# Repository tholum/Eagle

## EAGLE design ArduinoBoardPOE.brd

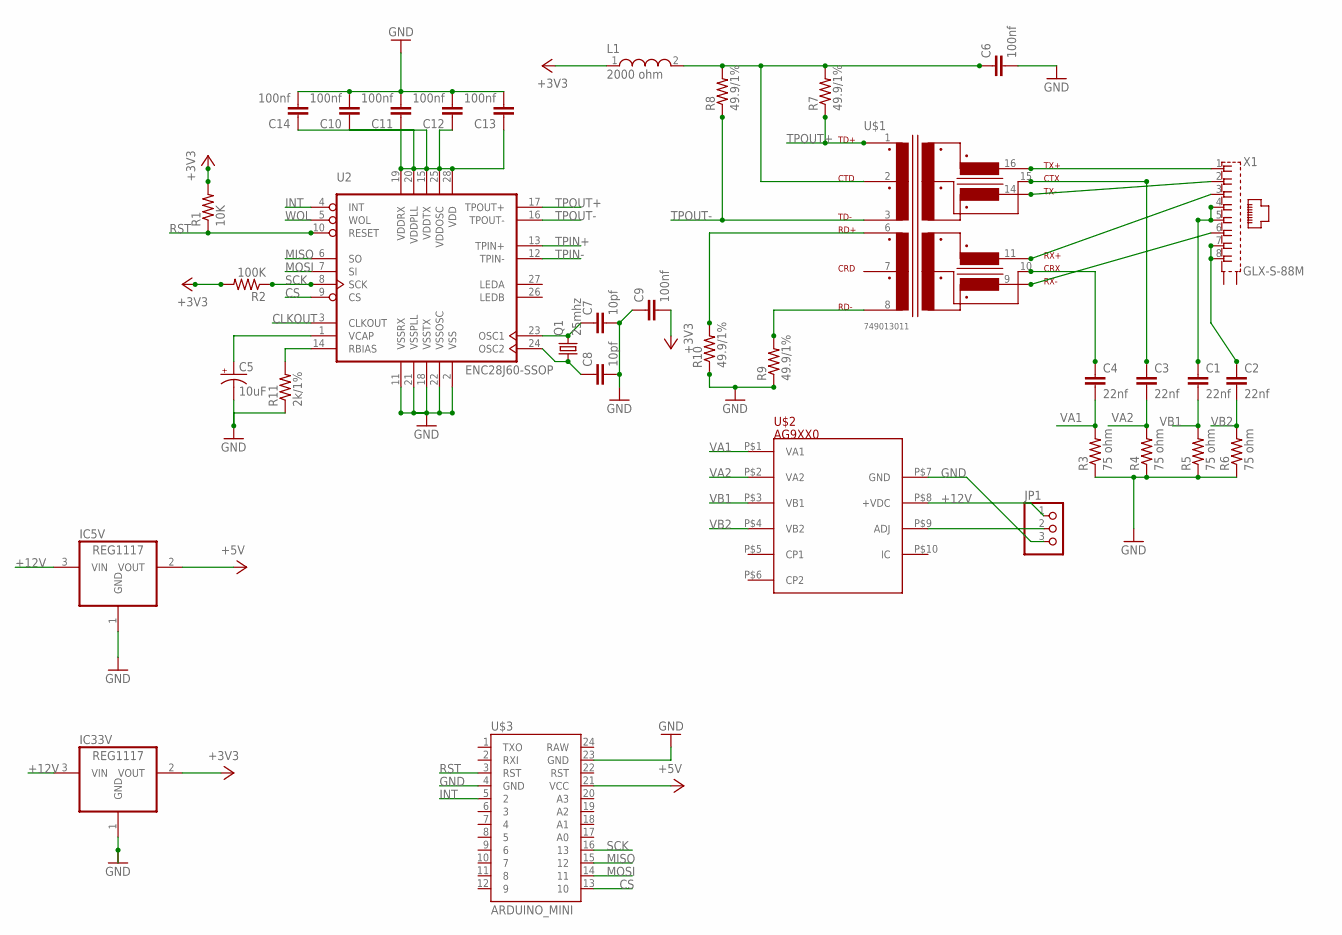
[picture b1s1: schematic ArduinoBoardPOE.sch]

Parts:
C1, C2, C3, C4: 22nf; 0805
C5: 10uF; EIA3216
C6, C9, C10, C11, C12, C13, C14: 100nf; 0805
C7, C8: 10pf; 0805
IC5V, IC33V: REG1117; SOT223
JP1: PINHD-1X3; 1X03
L1: 2000 ohm; WE-CBA_0805(W=3)
Q1: 25mhz; HC49UP
R1: 10K; 0805
R2: 100K; 0805
R3, R4, R5, R6: 75 ohm; 0805
R7, R8, R9, R10: 49.9/1%; 0805
R11: 2k/1%; R0805
U2: ENC28J60-SSOP; SSOP28
U$1: 749013011
U$2: AG9XX0; AG9000
U$3: ARDUINO_MINI
X1: GLX-S-88M

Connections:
+3V3: C9.2, IC33V.2 (VOUT), L1.1, R1.2, R2.2
+5V: IC5V.2 (VOUT), U$3.21 (VCC)
+12V: IC5V.3 (VIN), IC33V.3 (VIN), JP1.1, U$2.P$8 (+VDC)
CLKOUT: U2.3 (CLKOUT)
CS: U2.9 (CS), U$3.13 (10)
GND: C5.C (-), C6.2, C7.2, C8.2, C9.1, C10.2, C11.2, C12.2, C13.2, C14.2, IC5V.1 (GND), IC33V.1 (GND), JP1.3, R3.1, R4.1, R5.1, R6.1, R9.1, R10.1, R11.1, U2.2 (VSS), U2.11 (VSSRX), U2.18 (VSSTX), U2.21 (VSSPLL), U2.22 (VSSOSC), U$2.P$7 (GND), U$3.4 (GND), U$3.23 (GND)
INT: U2.4 (INT), U$3.5 (2)
MISO: U2.6 (SO), U$3.15 (12)
MOSI: U2.7 (SI), U$3.14 (11)
unnamed: U$1.16 (7), X1.1
unnamed: U$1.14 (9), X1.2
unnamed: U$1.11 (10), X1.3
unnamed: U$1.9 (12), X1.6
unnamed: C2.1, X1.7, X1.8
unnamed: C1.1, X1.4, X1.5
unnamed: C3.1, U$1.15 (8)
unnamed: C4.1, U$1.10 (11)
unnamed: C6.1, L1.2, R7.2, R8.2, U$1.2
unnamed: C7.1, Q1.2, U2.23 (OSC1)
unnamed: JP1.2, U$2.P$9 (ADJ)
unnamed: C8.1, Q1.1, U2.24 (OSC2)
unnamed: C10.1, C11.1, C12.1, C13.1, C14.1, U2.15 (VDDTX), U2.19 (VDDRX), U2.20 (VDDPLL), U2.25 (VDDOSC), U2.28 (VDD)
unnamed: C5.A (+), U2.1 (VCAP)
unnamed: R11.2, U2.14 (RBIAS)
RST: R1.1, U2.10 (RESET), U$3.3 (RST)
SCK: R2.1, U2.8 (SCK), U$3.16 (13)
TPIN+: R10.2, U2.13 (TPIN+), U$1.6 (4)
TPIN-: R9.2, U2.12 (TPIN-), U$1.8 (6)
TPOUT+: R7.1, U2.17 (TPOUT+), U$1.1
TPOUT-: R8.1, U2.16 (TPOUT-), U$1.3
VA1: C4.2, R3.2, U$2.P$1 (VA1)
VA2: C3.2, R4.2, U$2.P$2 (VA2)
VB1: C1.2, R5.2, U$2.P$3 (VB1)
VB2: C2.2, R6.2, U$2.P$4 (VB2)
WOL: U2.5 (WOL)

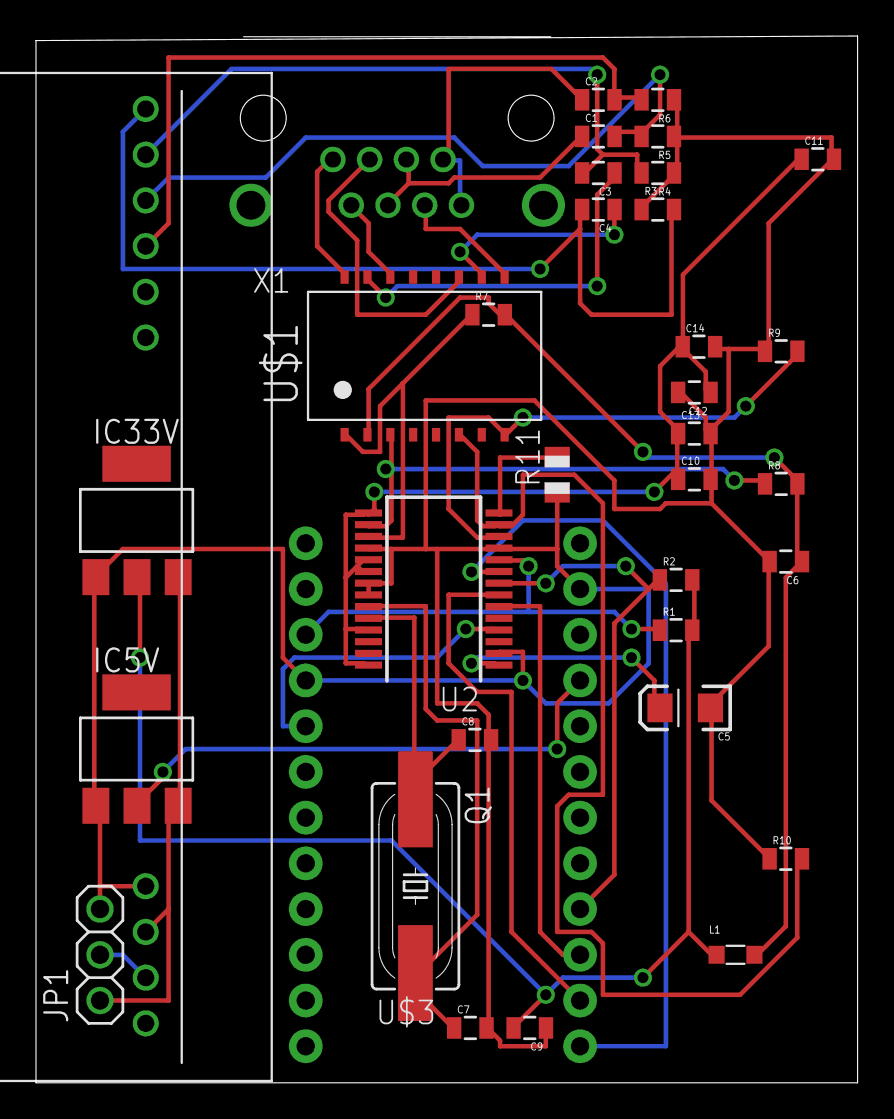
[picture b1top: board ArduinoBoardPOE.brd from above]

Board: 2 copper layers, 45.6 x 58.2 mm, 35 parts (0 on the bottom side), 33 nets.

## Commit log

2015-09-28 Adding Projects

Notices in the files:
parts and their libraries:
SparkFun-Capacitors: Licensing: Creative Commons ShareAlike 4.0 International - https://creativecommons.org/licenses/by-sa/4.0
SignalCommunications: Copyright: Würth Elektronik
Wurth_Electronics_Midcom_Speedy_and_stan: Copyright: Wurth Electronics Midcom, Inc.
